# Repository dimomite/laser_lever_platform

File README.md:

# laser lever platform
Platform for remote adjustment rotation and position of a laser level

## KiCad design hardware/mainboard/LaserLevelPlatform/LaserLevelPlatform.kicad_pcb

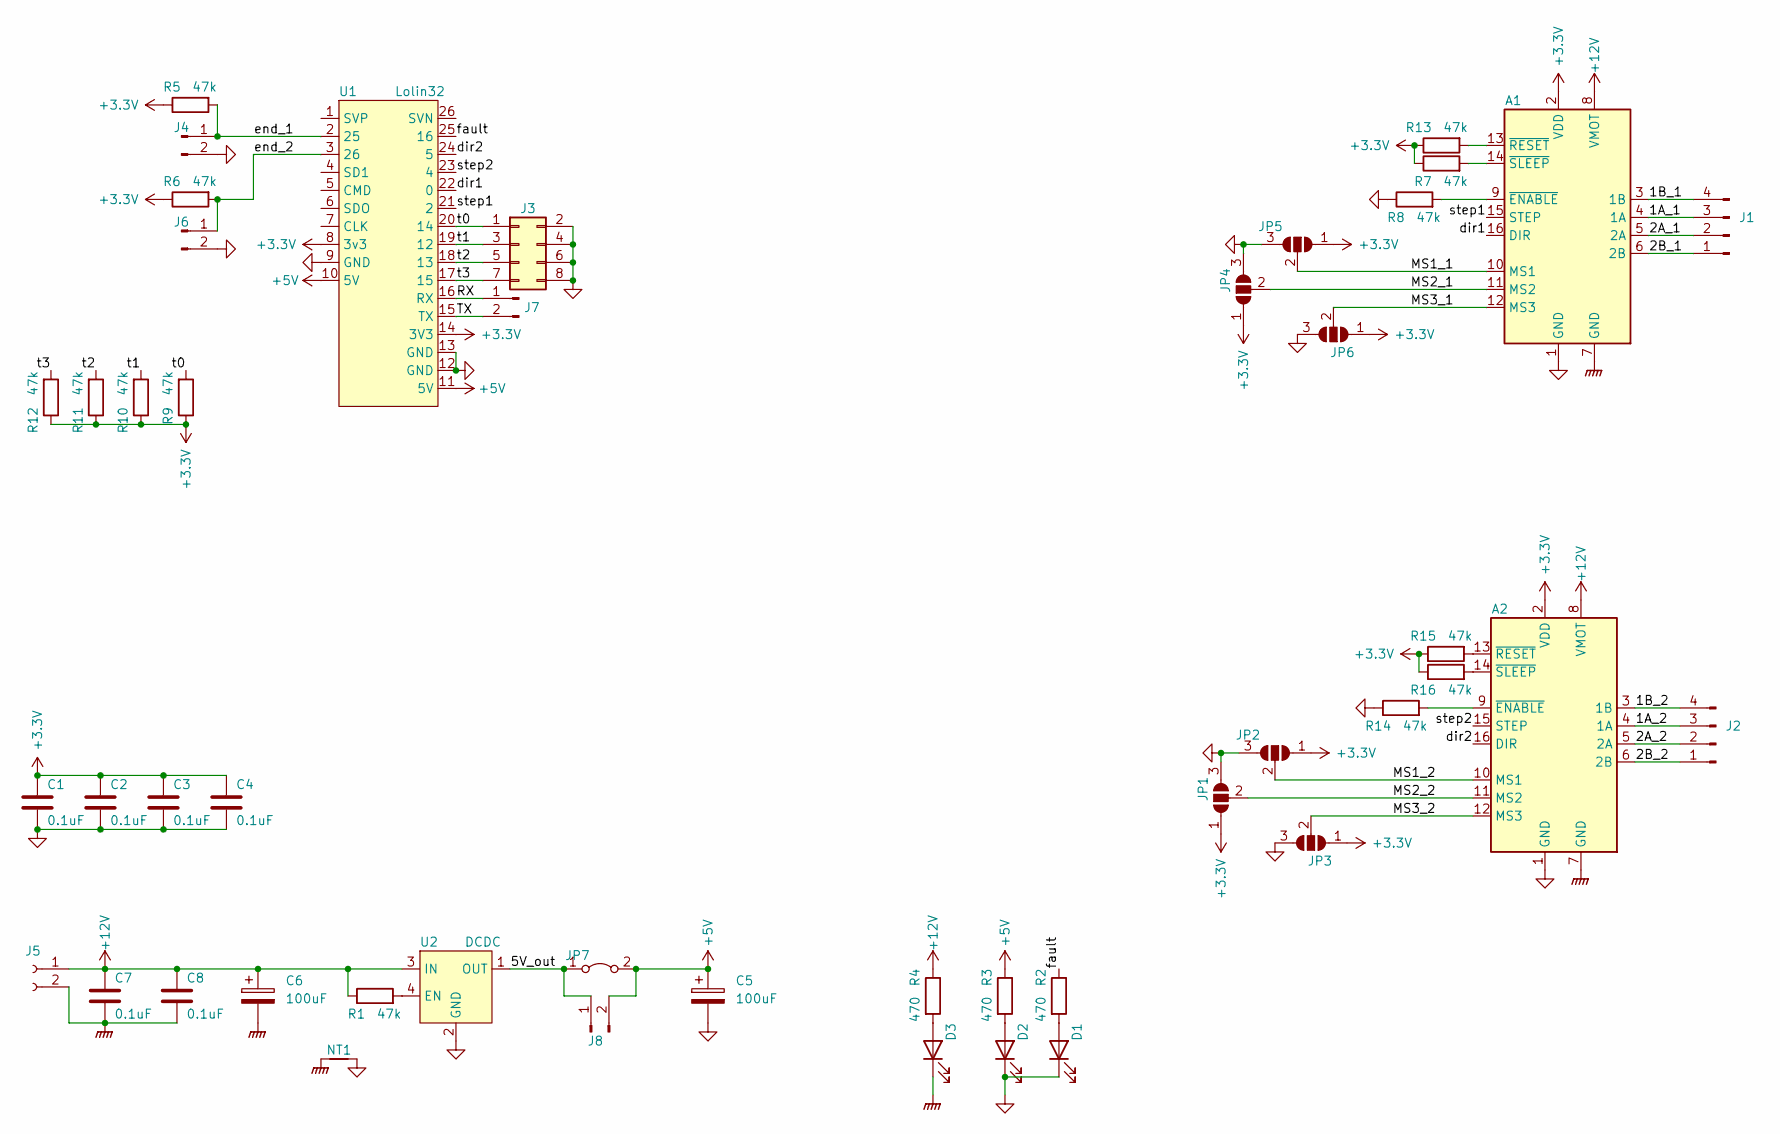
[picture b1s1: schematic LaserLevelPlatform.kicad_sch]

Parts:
A1, A2: Pololu_Breakout_A4988; Pololu_Breakout-16_15.2x20.3mm
C1, C2, C3, C4, C7, C8: 0.1uF; C_0805_2012Metric_Pad1.18x1.45mm_HandSolder
C5: 100uF; CP_Radial_D10.0mm_P2.50mm_P5.00mm
C6: 100uF; CP_Radial_D10.0mm_P5.00mm
D1, D2, D3: LED; LED_D5.0mm
J1, J2: Conn_01x04_Male; JST_EH_B4B-EH-A_1x04_P2.50mm_Vertical
J3: Conn_02x04_Odd_Even; PinHeader_2x04_P2.54mm_Vertical
J4, J6: Conn_01x02_Male; JST_EH_B2B-EH-A_1x02_P2.50mm_Vertical
J5: Conn_01x02_Female; PhoenixContact_MSTBVA_2,5_2-G-5,08_1x02_P5.08mm_Vertical
J7, J8: Conn_01x02_Male; PinHeader_1x02_P2.54mm_Vertical
JP1, JP2, JP3, JP4, JP5, JP6: SolderJumper_3_Open; SolderJumper-3_P2.0mm_Open_TrianglePad1.0x1.5mm
JP7: Jumper_2_Bridged; SolderJumper-2_P1.3mm_Open_TrianglePad1.0x1.5mm
NT1: NetTie_2; NetTie-2_SMD_Pad2.0mm
R1, R5, R6, R7, R8, R9, R10, R11, R12, R13, R14, R15, R16: 47k; R_0805_2012Metric_Pad1.20x1.40mm_HandSolder
R2, R3, R4: 470; R_0805_2012Metric_Pad1.20x1.40mm_HandSolder
U1: Lolin32
U2: DCDC

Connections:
+3.3V: A1.2 (VDD), A2.2 (VDD), C1.1, C2.1, C3.1, C4.1, JP1.1 (A), JP2.1 (A), JP3.1 (A), JP4.1 (A), JP5.1 (A), JP6.1 (A), R5.1, R6.1, R7.1, R9.1, R10.1, R11.1, R12.1, R13.1, R15.1, R16.1, U1.8 (3v3), U1.14 (3V3)
+5V: C5.1, J8.2, JP7.2 (B), R3.1, U1.10 (5V), U1.11 (5V)
+12V: A1.8 (VMOT), A2.8 (VMOT), C6.1, C7.1, C8.1, J5.1, R1.1, R4.1, U2.3 (IN)
/1A_1: A1.4 (1A), J1.3
/1A_2: A2.4 (1A), J2.3
/1B_1: A1.3 (1B), J1.4
/1B_2: A2.3 (1B), J2.4
/2A_1: A1.5 (2A), J1.2
/2A_2: A2.5 (2A), J2.2
/2B_1: A1.6 (2B), J1.1
/2B_2: A2.6 (2B), J2.1
/5V_out: J8.1, JP7.1 (A), U2.1 (OUT)
/MS1_1: A1.10 (MS1), JP5.2 (C)
/MS1_2: A2.10 (MS1), JP2.2 (C)
/MS2_1: A1.11 (MS2), JP4.2 (C)
/MS2_2: A2.11 (MS2), JP1.2 (C)
/MS3_1: A1.12 (MS3), JP6.2 (C)
/MS3_2: A2.12 (MS3), JP3.2 (C)
/RX: J7.1, U1.16 (RX)
/TX: J7.2, U1.15 (TX)
/dir1: A1.16 (DIR), U1.22 (0)
/dir2: A2.16 (DIR), U1.24 (5)
/end_1: J4.1, R5.2, U1.2 (25)
/end_2: J6.1, R6.2, U1.3 (26)
/fault: R2.1, U1.25 (16)
/step1: A1.15 (STEP), U1.21 (2)
/step2: A2.15 (STEP), U1.23 (4)
/t0: J3.1, R9.2, U1.20 (14)
/t1: J3.3, R10.2, U1.19 (12)
/t2: J3.5, R11.2, U1.18 (13)
/t3: J3.7, R12.2, U1.17 (15)
GND: A1.1 (GND), A2.1 (GND), C1.2, C2.2, C3.2, C4.2, C5.2, D1.1 (K), D2.1 (K), J3.2, J3.4, J3.6, J3.8, J4.2, J6.2, JP1.3 (B), JP2.3 (B), JP3.3 (B), JP4.3 (B), JP5.3 (B), JP6.3 (B), NT1.2, R8.1, R14.1, U1.9 (GND), U1.12 (GND), U1.13 (GND), U2.2 (GND)
GNDPWR: A1.7 (GND), A2.7 (GND), C6.2, C7.2, C8.2, D3.1 (K), J5.2, NT1.1
unnamed: A1.9 (~ENABLE), R8.2
unnamed: A1.13 (~RESET), R13.2
unnamed: A1.14 (~SLEEP), R7.2
unnamed: A2.9 (~ENABLE), R14.2
unnamed: A2.13 (~RESET), R15.2
unnamed: A2.14 (~SLEEP), R16.2
unnamed: D1.2 (A), R2.2
unnamed: D2.2 (A), R3.2
unnamed: D3.2 (A), R4.2
unnamed: R1.2, U2.4 (EN)

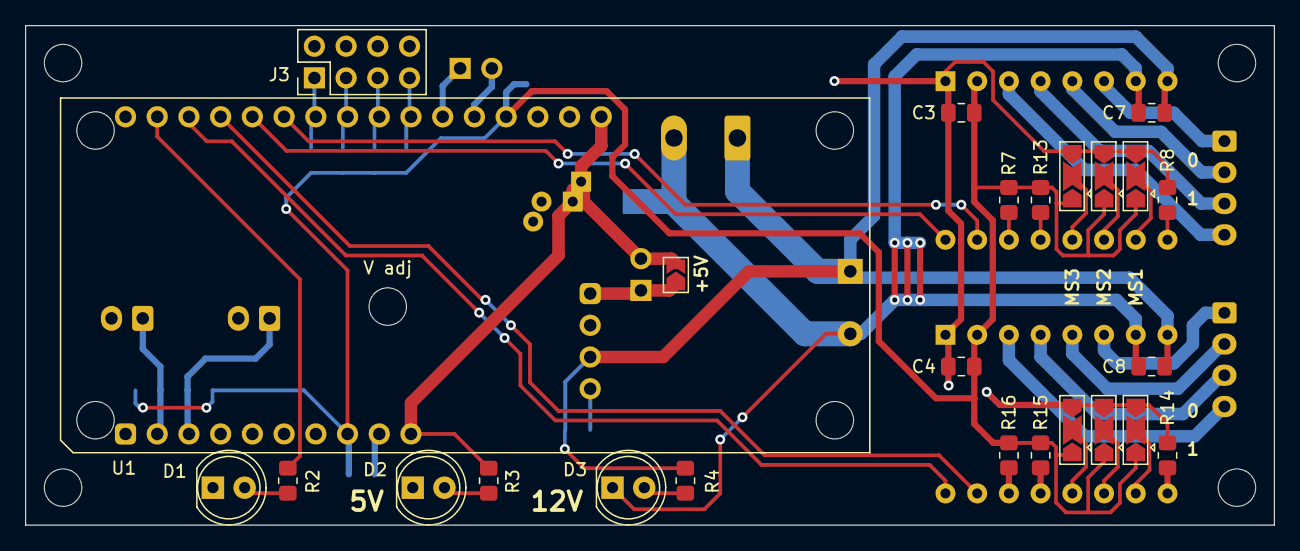
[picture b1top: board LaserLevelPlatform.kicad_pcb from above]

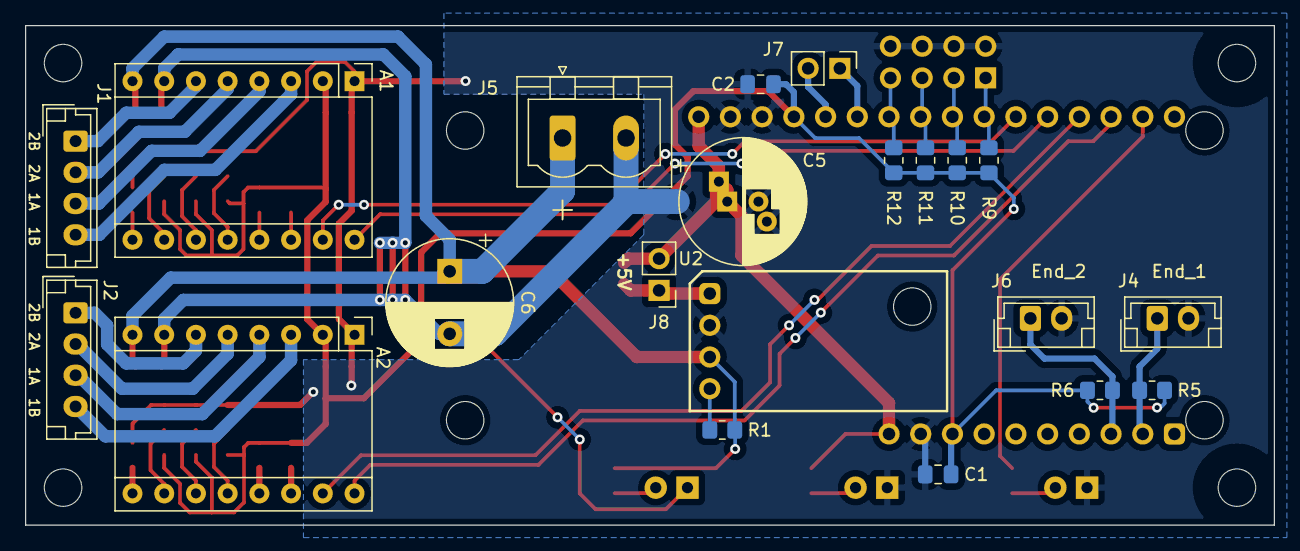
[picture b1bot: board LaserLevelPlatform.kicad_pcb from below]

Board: 2 copper layers, 100.0 x 40.0 mm, 47 parts (22 on the bottom side), 43 nets.

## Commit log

2022-08-19 Add first implementation
    Added:
    - motor control by hardware buttons/switches
    - support for end stops; error signal when both are active
    simultaniously
    - test connection to the onboard OLED indicator
    - WiFi soft access point implementation
2022-08-21 Start async web server impl
    Increase image size to >3MB
    Add simple implementation of a WebServer:
    - /hello
    - /api/status
    - /favicon.ico
    - not implemented URLs logging
2022-08-24 Initial app commit
    Add control application initial setup.
    Add Hilt and RxJava to dependencies.
2022-08-24 Add local rxjava flow
    Add mini-repo and debug flow updating data every 1 second.
    Add logging with Timber lib.
2022-08-26 Read data from device
    Add Retrofit and Moshi dependencies.
    Add data flow provider reading data from the device.
2022-08-27 Display platform status
2022-08-27 Report platform status
2022-09-08 PCB design
    Add schematic and pcb.
2022-09-18 Change outputs to match PCB
    Change application to work on manufactured PCB. It reacts on touch
    events and send output signals for stepper motor. Data is updated approx
    every 50ms. No PWM or interrupts are used at the moment.
2022-09-18 Add jumper on +5V line
    Add a jumper to disconnect +5V power line from DC-DC converter from the
    main CPU board. This is needed for safe connection of a USB power
    together with a +12V input. Also added a bridge in parallel to it for
    the permanent connection.
2022-09-19 Add "fp-info-cache" to gitignore
2022-10-24 Change movement control to stepper motors
2022-11-09 Add remote control from Android app
2022-11-27 Movement commands handling improvement
    Extend remote control with duration definition.
    Improve movement commands handling by the platform
2022-11-27 Fix app crashes on lost connection
    Catch IOExceptions from remote requests to prevent app from crashing.
2022-11-27 Add stop command
2022-12-17 Remove dead code
2022-12-18 Add web-inteface for platform movement control
2023-01-21 Display AP pass and server address
